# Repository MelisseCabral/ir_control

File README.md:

# Acionamento por IR com Dispositivo Atuador Genérico

Melisse P. Cabral;
Julio Cesar Ferreira Lima;
José Lucas Damasceno Holanda;
Eric Guimarães Barbosa;
João Lucas de Oliveira Torres

Universidade Federal do Ceará, Sobral, Brasil

melissecabral@gmail.com;
julio\_flima@hotmail.com ; 
lucasholanda95@gmail.com;
ericguimaraes@msn.com;

**Abstract — This report proposes to present the development of a residential automation destined to be manufactured in the Brazilian industry. They were used to carry out the project by developing free software like Arduino IDE. During the report, several development environments will be presented, targeting not only the hardware, but also the software and the results of the final object. **

**Key-words: home automation; Arduino; IRremote; TSOP **

## Introdução

A crescente busca por dispositivos automatizados aquece o mercado de tecnologia em
todo mundo. Entretanto dispositivos de automação residencial ainda não se estabeleceram no
mercado brasileiro devido aos seus altos custos de produção quando equiparados ao poder de
compra médio. Pensando nisso foi concebido um dispositivo que pudesse trazer a automação
para a realidade brasileira.

A proposta desse trabalho é trazer um dispositivo de automativo de simples instalação
e uso a um baixo custo. Nesse intuito foi escolhida uma tecnologia robusta que propocionasse
tal advento, o a comunicação por infravermelho.

Os sensores infravermelhos utilizados na recepção de dados proporcionam uma série
de vantagens quando comparado a outros tipos de comunicação sem fio, como baixo custo,
simplicidade de implementação e sua baixa vulnerabilidade a ruídos externos, desse modo é
considerado um tipo de comunicação robusta (HAYKIN; VEEN, 2003).

Paralelo a isso, o controle remoto é um objeto comum a vários dispositivos eletrônicos
presentes no cotidiano, em sua maioria é comum encontrar teclas que não possuem nenhuma
funcionalidade, mas com este dispositivo é possível atribuir funcionalidade a tais teclas. Isso
se dá devido aos botões programáveis contidos no dispositivo, tornando assim possível a troca
de controles ou até mesmo uma melhor configurações de teclas. Ao manter-los pressionados,
esperarão receber um novo valor de tecla, passado pelo controle remoto e cadastra-lo-á.
Assim ao sempre que a tecla cadastrada for pressionada, será acionado algum
eletredoméstico, por ventura ligado ao dispositivo.

## Metodologia

No projeto foi utilizado um módulo de sensor infravermelho TSOP 1738
(TELEFUNKEN, 1998), permitindo a comunicação entre o Arduino (Arduino, 2017) e um
controle remoto. O modelo utilizado foi o Arduino Pro Mini, usado para recepção de dados
provenientes do TSOP e o controle de acionamentos que são possíveis por meio de relés,
resistores, transistores e diodos. Por conseguinte, foram utilizados dois botões para sinalizar a
gravação do botão desejado e um controle remoto genérico para ligar e desligar os
equipamentos conectados ao dispositivo desenvolvido.

A tecnologia de infravermelho é um protocolo de transmissão sem fio de dados usados
para controlar e operar diversos dispositivos. A transferência de dados de infravermelho é
implementada de acordo com os protocolos e os padrões da IrDA (Infrared Data Association). 
Esses padrões são projetados para aceitar componentes de baixo custo, reduzir a demanda de
energia e para ativar conexões simplesmente apontando dispositivos de infravermelho um para
o outro (BARKER, et al, 2002).

Em meio aos vários protocolos de comunicação IR existentes, todos possuem objetivos
em comum como: velocidade do canal completo, segurança, baixo custo, baixa manutenção,
circuitos de fácil implementação, mas diferenciam-se no modo de comunicação e na
transmissão dos dados tendo variações no número de instruções, tamanho da palavra de bits
transmitida, no consumo de energia, compatibilidade com dispositivos eletrônicos, faixa de
frequência de operação e etc. (HAYKIN; MOHER, 2010).

O protocolo Consumer Infrared (CIR) utiliza LEDs infravermelho que nada mais são
do que diodos emissores de luz no comprimento de onda do infravermelho, utiliza também
receptores infravermelhos de encapsulamento único, que são circuitos integrados
optoeletrônicos. Tais receptores possuem toda a etapa óptica, lente, transdutor, etapa
eletrônica, filtro passa-faixa e amplificador, necessária para realizar a recepção e demodulação
do sinal infravermelho sem maiores complicações (KAHN, 1994).

O Arduino Pro Mini foi utilizado dado que trata de uma plataforma de desenvolvimento
provisória destinada a protótipos. Possui quatorze portas digitais e seis portas as analógicas que
podem ser utilizadas para recepção e envio de dados. O modelo o ATmega168 possui tensão
de alimentação de 5V, com uma memória flash de apenas 16 KB, o que é suficiente para a
programação do dispositivo. Esse modelo de microcontrolador possui um clock de 16 MHz
que atendeu bem as necessidades do protótipo.

As portas digitais do circuito integrado ATmega168 funcionam na faixa de tensão de 0
a 5V. Desse modo as entradas digitais D2 e D3 receberão borda de subida quando uma chave
1 ou uma chave 2 for pressionada. No entanto, é necessário implementar um resistor de
pulldown e um capacitor debouncer, em paralelo, com o intuito de garantir que o as portas
digitais recebam unicamente borda de subida ou de descida. Isso é necessário para evitar o
efeito bouncing e erros de leitura pelas portas de entrada do microcontrolador. Este resistor
permite que, enquanto a chave não esteja pressionada, a porta digital permaneça em nível
baixo ativo. Quando a chave é pressionada, no nó entre o resistor e a chave, há 5V. Porém, se
a tensão variar por conta do efeito bouncing na chave, o capacitor mantém a tensão em 5V,
garantindo a borda de subida e diluindo o ruído no filtro.

O dispositivo relé atua como intermediador entre o microcontrolador e os aparelhos
que se desejam controlar. Este dispositivo é na verdade um interruptor que é acionado de
acordo com a corrente que percorre sua bobina, permitindo que o relé seja acionado, e
aparelhos que funcionam em elevadas tensões sejam controlados.
O microcontrolador foi programado utilizando a IDE Arduino, que é uma plataforma
de desenvolvimento de código aberto disponibilizada no GitHub. A plataforma pode ser
utilizada para a programação de qualquer Arduino utilizando a linguagem C e possui diversas
bibliotecas disponíveis para a integração de inúmeros módulos e sensores.
Para interfacear a comunicação infravermelha foi utilizada a biblioteca “IRremote”.
Após a inserção da biblioteca é necessário declarar o “IRrecev” responsável por ser o receptor
de dados, informando o pino o qual está conectado o TSOP, a partir deste ponto já estamos
aptos a receber os dados. Foi necessário também declarar o “decode_results” que é o
responsável por decodificar os dados enviados ao Arduino pela porta digital na qual está
conectada o TSOP.

A programação em C foi feita de modo estruturada, para projetos maiores também
pode ser feito o uso de orientação a objeto. O código foi escrito e refatorado de modo a ficar
de fácil manutenção, coeso e com um baixo acoplamento.
A função de reprogramação de teclas, por sua vez, é acionada por botões ligados a
portas digitais, que ao serem pressionados iniciam uma nova rotina de duração predefinida 
onde aguarda uma nova entrada de dados pelo TSOP em um tempo predefinido, caso seja
recebido algum valor pelo sensor esse novo valor será associado a variável de acionamento
que corresponda ao botão pressionado, caso não receba nenhum dado até o fim do tempo
definido, nada acontece.

### Indicativo de aplicabilidade
O aumento em busca de novas tecnologias que possam simplificar o uso de aparelhos eletrônicos no cotidiano propulsiona o mercado de automação e controle. E essa busca que inicialmente partiu para setor industrial excitou o público em geral a cada vez mais procurar itens que sejam automatizados, de modo que possa proporcionar um maior conforto em suas residências.  Pensando nessa necessidade de mercado foi idealizado um dispositivo de acionamento genérico, de modo a atender a diversas aplicações com um baixo custo de aquisição.

A comunicação infravermelha possui vantagens em meio a outras tecnologias de comunicação sem fio, como o baixo custo que foi um fator chave para a concepção de um protótipo que garante bons resultados a custos que tornam a automação residencial possível para o mercado brasileiro.  O dispositivo foi desenvolvido pensando em um ambiente como uma sala de tv ou quarto, para efetuar o controle de dispositivos comuns a estes ambientes em lares brasileiros como o um abajur e um ventilador. Assim ao efetuar o controle a distância, o dispositivo proporciona conforto ao usuário. Esta é a máxima agregadora de valor ao produto. 

## Resultados e Discussões 

A comunicação por infravermelho possui vantagens em meio a outras tecnologias de
comunicação sem fio, como o baixo custo que foi um fator chave para a concepção de um
protótipo que garante bons resultados a custos que tornam a automação residencial possível
para o mercado brasileiro.

Por se tratar de um protótipo, o circuito foi montado em uma placa perfurada de
fenolite, que é composta por uma matriz de furos e ilhas isoladas, de modo que as trilhas do
circuito são feitas utilizando preenchimento com solda eletrônica em locais onde há a
possibilidade de passagem de alta corrente ou fios para contatos de baixa corrente. Essa
escolha foi influenciada pela facilidade no desenvolvimento da placa, pois o processo de
desenvolvimento de uma placa de circuito impresso seria dispendioso e oneroso quanto a
criação do design. A distribuição de componentes foi pensada para otimizar o espaço a fim de
que o dispositivo pudesse ser encaixado na caixa idealizada.

Foi utilizado o conceito “design clean” (Aponto Design, 2016), onde se preza pelo
aspecto limpo com poucos ou nenhum ornamento, mantendo apenas aquilo é necessário,
causando de pouca a nenhuma interferência nos ambientes em que foram inseridos.

## Conclusão

O dispositivo foi desenvolvido pensando em um ambiente como uma sala de tv ou
quarto, para efetuar o controle de dispositivos comuns a estes ambientes em lares brasileiros
como o um abajur e um ventilador. Assim ao efetuar o controle a distância, o dispositivo
proporciona conforto ao usuário.
O protótipo desenvolvido está em uso a cerca de quatro meses em um ventilador de
uso diário, e desde então não foram constatadas nenhuma falha. O dispositivo desenvolvido
mostrou-se eficiente e econômico.
Os objetivos supracitados foram alcançados pelo protótipo, como a possibilidade de
ser adquirido por pessoas de baixo poder de compra e a difusão 

## Referência

1. Aponto Design, Clean não é Branco, 2016. Disponível em:
<http://apontodesign.com/blog/clean-nao-e-branco/>. Acesso em 20 de Abril de 2016.

2. Arduino, Language Reference, 2017. Disponível em:
<https://www.arduino.cc/en/Reference/HomePage>. Acesso em 20 de Abril de 2016

3. BARKER, P.; BOUCOUVALAS, A.C.; VITSAS, V. Performance modelling of the IrDA
infrared wireless communications protocol. In International Journal of Communication
Systems. 2002.

4. HAYKIN, S.; MOHER, M. Sistemas de Comunicação. Editora Bookman; 5ª Edição, 2010.
HAYKIN, S.; VEEN, B. V.; Signals and Systems. Editora John Wiley and Sons; 2ª Edição,
2003.

5. Vishay Telefunken. Photo Modules for PCM Remote Control Systems, TSOP17, datasheet,
Dez. 1998.

6. KAHN, J. M.; BARRY, J. R.. Wireless Infrared Communications. Springer US, 1994.

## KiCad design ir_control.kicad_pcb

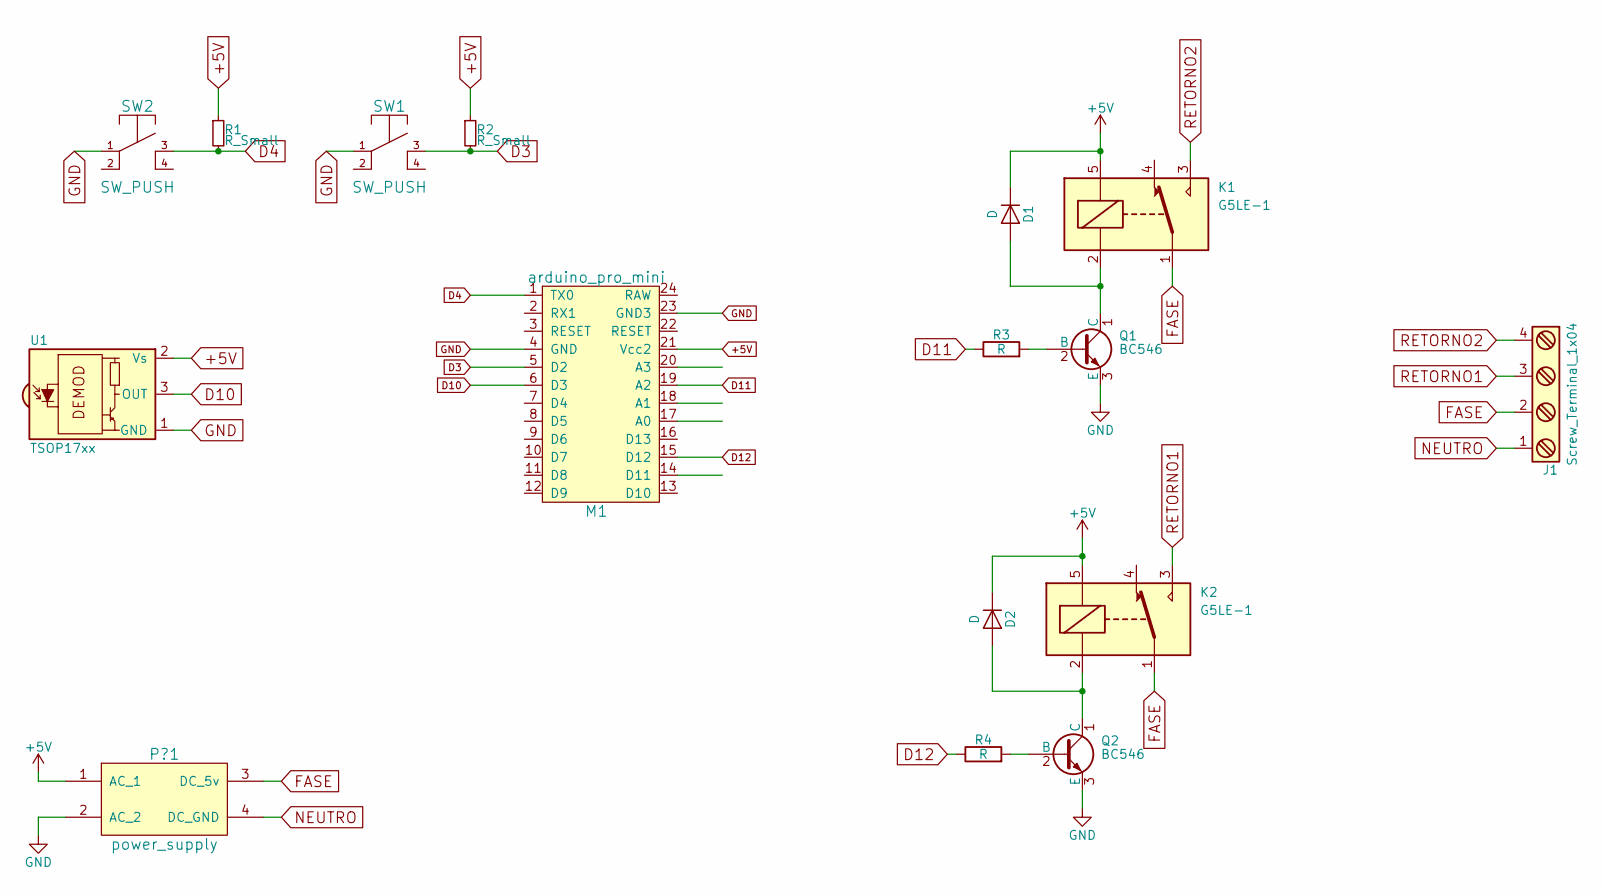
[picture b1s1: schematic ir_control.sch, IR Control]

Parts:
D1, D2: D; D_DO-15_P5.08mm_Vertical_AnodeUp
J1: Screw_Terminal_1x04; TerminalBlock_Pheonix_MKDS1.5-4pol
K1, K2: G5LE-1; Relay_SPDT_Omron-G5LE-1
M1: arduino_pro_mini
P?1: power_supply
Q1, Q2: BC546; TO-92_Molded_Wide_Oval
R1, R2: R_Small; R_Axial_DIN0207_L6.3mm_D2.5mm_P7.62mm_Horizontal
R3, R4: R; R_Axial_DIN0207_L6.3mm_D2.5mm_P7.62mm_Horizontal
SW1, SW2: SW_PUSH; SW_PUSH_6mm_h4.3mm
U1: TSOP17xx; IRReceiver_Vishay_MOLD-3pin

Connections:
+5V: D1.1 (K), D2.1 (K), K1.5, K2.5, M1.21 (Vcc2), P?1.1 (AC_1), R1.1, R2.1, U1.2 (Vs)
D3: M1.5 (D2), R2.2, SW1.3
D4: M1.1 (TX0), R1.2, SW2.3
D10: M1.6 (D3), U1.3 (OUT)
D11: M1.19 (A2), R3.1
D12: M1.15 (D12), R4.1
FASE: J1.2, K1.1, K2.1, P?1.3 (DC_5v)
GND: M1.4 (GND), M1.23 (GND3), P?1.2 (AC_2), Q1.3 (E), Q2.3 (E), SW1.1, SW2.1, U1.1 (GND)
NEUTRO: J1.1, P?1.4 (DC_GND)
unnamed: D1.2 (A), K1.2, Q1.1 (C)
unnamed: D2.2 (A), K2.2, Q2.1 (C)
unnamed: Q1.2 (B), R3.2
unnamed: Q2.2 (B), R4.2
RETORNO1: J1.3, K2.3
RETORNO2: J1.4, K1.3

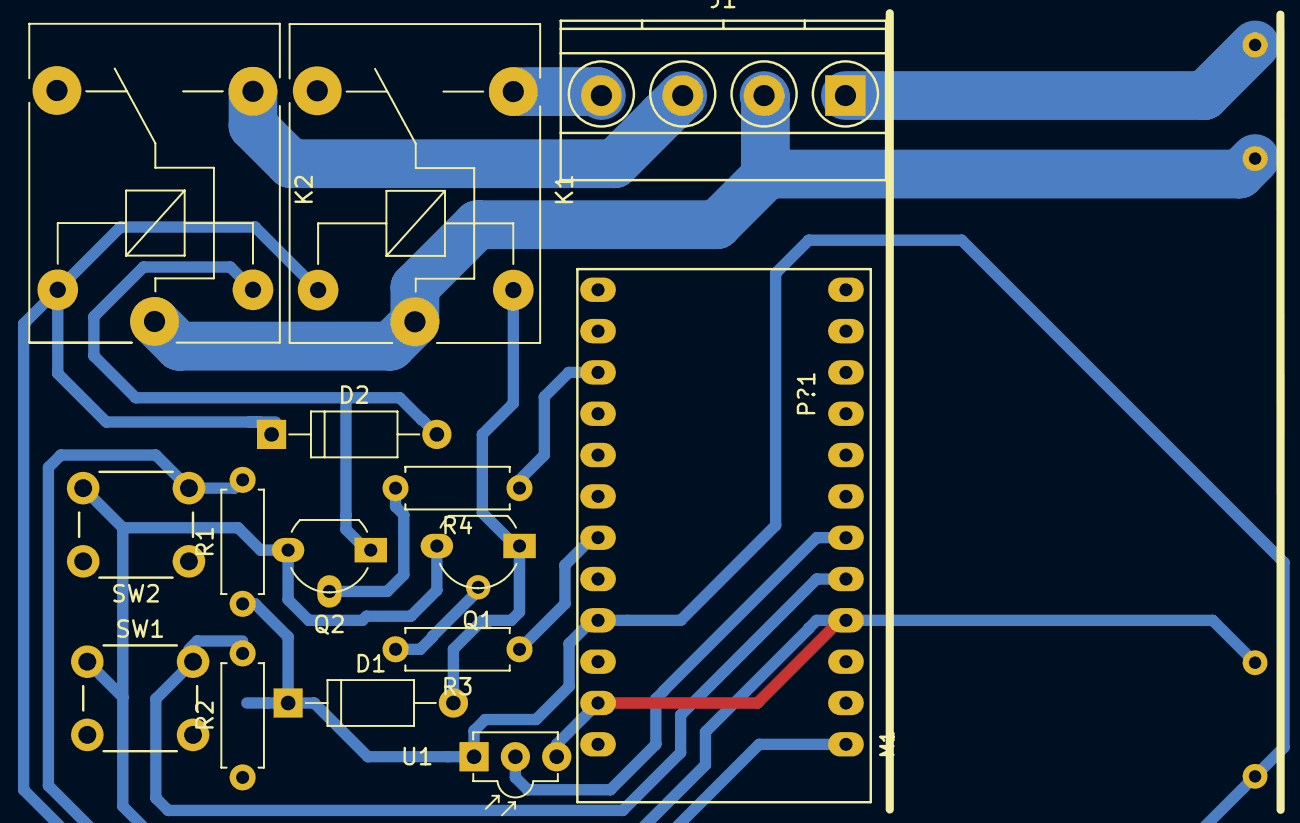
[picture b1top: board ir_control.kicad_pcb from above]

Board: 2 copper layers, 16 parts (0 on the bottom side), 15 nets.
